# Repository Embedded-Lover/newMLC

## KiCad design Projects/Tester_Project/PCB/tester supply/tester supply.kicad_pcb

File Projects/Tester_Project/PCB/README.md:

# Analog_box_IO_Tester_Hardware

## Getting started

To make it easy for you to get started with GitLab, here's a list of recommended next steps.

Already a pro? Just edit this README.md and make it your own. Want to make it easy? [Use the template at the bottom](#editing-this-readme)!

## Add your files

- [ ] [Create](https://docs.gitlab.com/ee/user/project/repository/web_editor.html#create-a-file) or [upload](https://docs.gitlab.com/ee/user/project/repository/web_editor.html#upload-a-file) files
- [ ] [Add files using the command line](https://docs.gitlab.com/ee/gitlab-basics/add-file.html#add-a-file-using-the-command-line) or push an existing Git repository with the following command:

```
cd existing_repo
git remote add origin https://git.mapnalocomotive.com/ahmadi_y/analog_box_io_tester_hardware.git
git branch -M main
git push -uf origin main
```

## Integrate with your tools

- [ ] [Set up project integrations](https://git.mapnalocomotive.com/ahmadi_y/analog_box_io_tester_hardware/-/settings/integrations)

## Collaborate with your team

- [ ] [Invite team members and collaborators](https://docs.gitlab.com/ee/user/project/members/)
- [ ] [Create a new merge request](https://docs.gitlab.com/ee/user/project/merge_requests/creating_merge_requests.html)
- [ ] [Automatically close issues from merge requests](https://docs.gitlab.com/ee/user/project/issues/managing_issues.html#closing-issues-automatically)
- [ ] [Enable merge request approvals](https://docs.gitlab.com/ee/user/project/merge_requests/approvals/)
- [ ] [Set auto-merge](https://docs.gitlab.com/ee/user/project/merge_requests/merge_when_pipeline_succeeds.html)

## Test and Deploy

Use the built-in continuous integration in GitLab.

- [ ] [Get started with GitLab CI/CD](https://docs.gitlab.com/ee/ci/quick_start/index.html)
- [ ] [Analyze your code for known vulnerabilities with Static Application Security Testing (SAST)](https://docs.gitlab.com/ee/user/application_security/sast/)
- [ ] [Deploy to Kubernetes, Amazon EC2, or Amazon ECS using Auto Deploy](https://docs.gitlab.com/ee/topics/autodevops/requirements.html)
- [ ] [Use pull-based deployments for improved Kubernetes management](https://docs.gitlab.com/ee/user/clusters/agent/)
- [ ] [Set up protected environments](https://docs.gitlab.com/ee/ci/environments/protected_environments.html)

***

# Editing this README

When you're ready to make this README your own, just edit this file and use the handy template below (or feel free to structure it however you want - this is just a starting point!). Thanks to [makeareadme.com](https://www.makeareadme.com/) for this template.

## Suggestions for a good README

Every project is different, so consider which of these sections apply to yours. The sections used in the template are suggestions for most open source projects. Also keep in mind that while a README can be too long and detailed, too long is better than too short. If you think your README is too long, consider utilizing another form of documentation rather than cutting out information.

## Name
Choose a self-explaining name for your project.

## Description
Let people know what your project can do specifically. Provide context and add a link to any reference visitors might be unfamiliar with. A list of Features or a Background subsection can also be added here. If there are alternatives to your project, this is a good place to list differentiating factors.

## Badges
On some READMEs, you may see small images that convey metadata, such as whether or not all the tests are passing for the project. You can use Shields to add some to your README. Many services also have instructions for adding a badge.

## Visuals
Depending on what you are making, it can be a good idea to include screenshots or even a video (you'll frequently see GIFs rather than actual videos). Tools like ttygif can help, but check out Asciinema for a more sophisticated method.

## Installation
Within a particular ecosystem, there may be a common way of installing things, such as using Yarn, NuGet, or Homebrew. However, consider the possibility that whoever is reading your README is a novice and would like more guidance. Listing specific steps helps remove ambiguity and gets people to using your project as quickly as possible. If it only runs in a specific context like a particular programming language version or operating system or has dependencies that have to be installed manually, also add a Requirements subsection.

## Usage
Use examples liberally, and show the expected output if you can. It's helpful to have inline the smallest example of usage that you can demonstrate, while providing links to more sophisticated examples if they are too long to reasonably include in the README.

## Support
Tell people where they can go to for help. It can be any combination of an issue tracker, a chat room, an email address, etc.

## Roadmap
If you have ideas for releases in the future, it is a good idea to list them in the README.

## Contributing
State if you are open to contributions and what your requirements are for accepting them.

For people who want to make changes to your project, it's helpful to have some documentation on how to get started. Perhaps there is a script that they should run or some environment variables that they need to set. Make these steps explicit. These instructions could also be useful to your future self.

You can also document commands to lint the code or run tests. These steps help to ensure high code quality and reduce the likelihood that the changes inadvertently break something. Having instructions for running tests is especially helpful if it requires external setup, such as starting a Selenium server for testing in a browser.

## Authors and acknowledgment
Show your appreciation to those who have contributed to the project.

## License
For open source projects, say how it is licensed.

## Project status
If you have run out of energy or time for your project, put a note at the top of the README saying that development has slowed down or stopped completely. Someone may choose to fork your project or volunteer to step in as a maintainer or owner, allowing your project to keep going. You can also make an explicit request for maintainers.

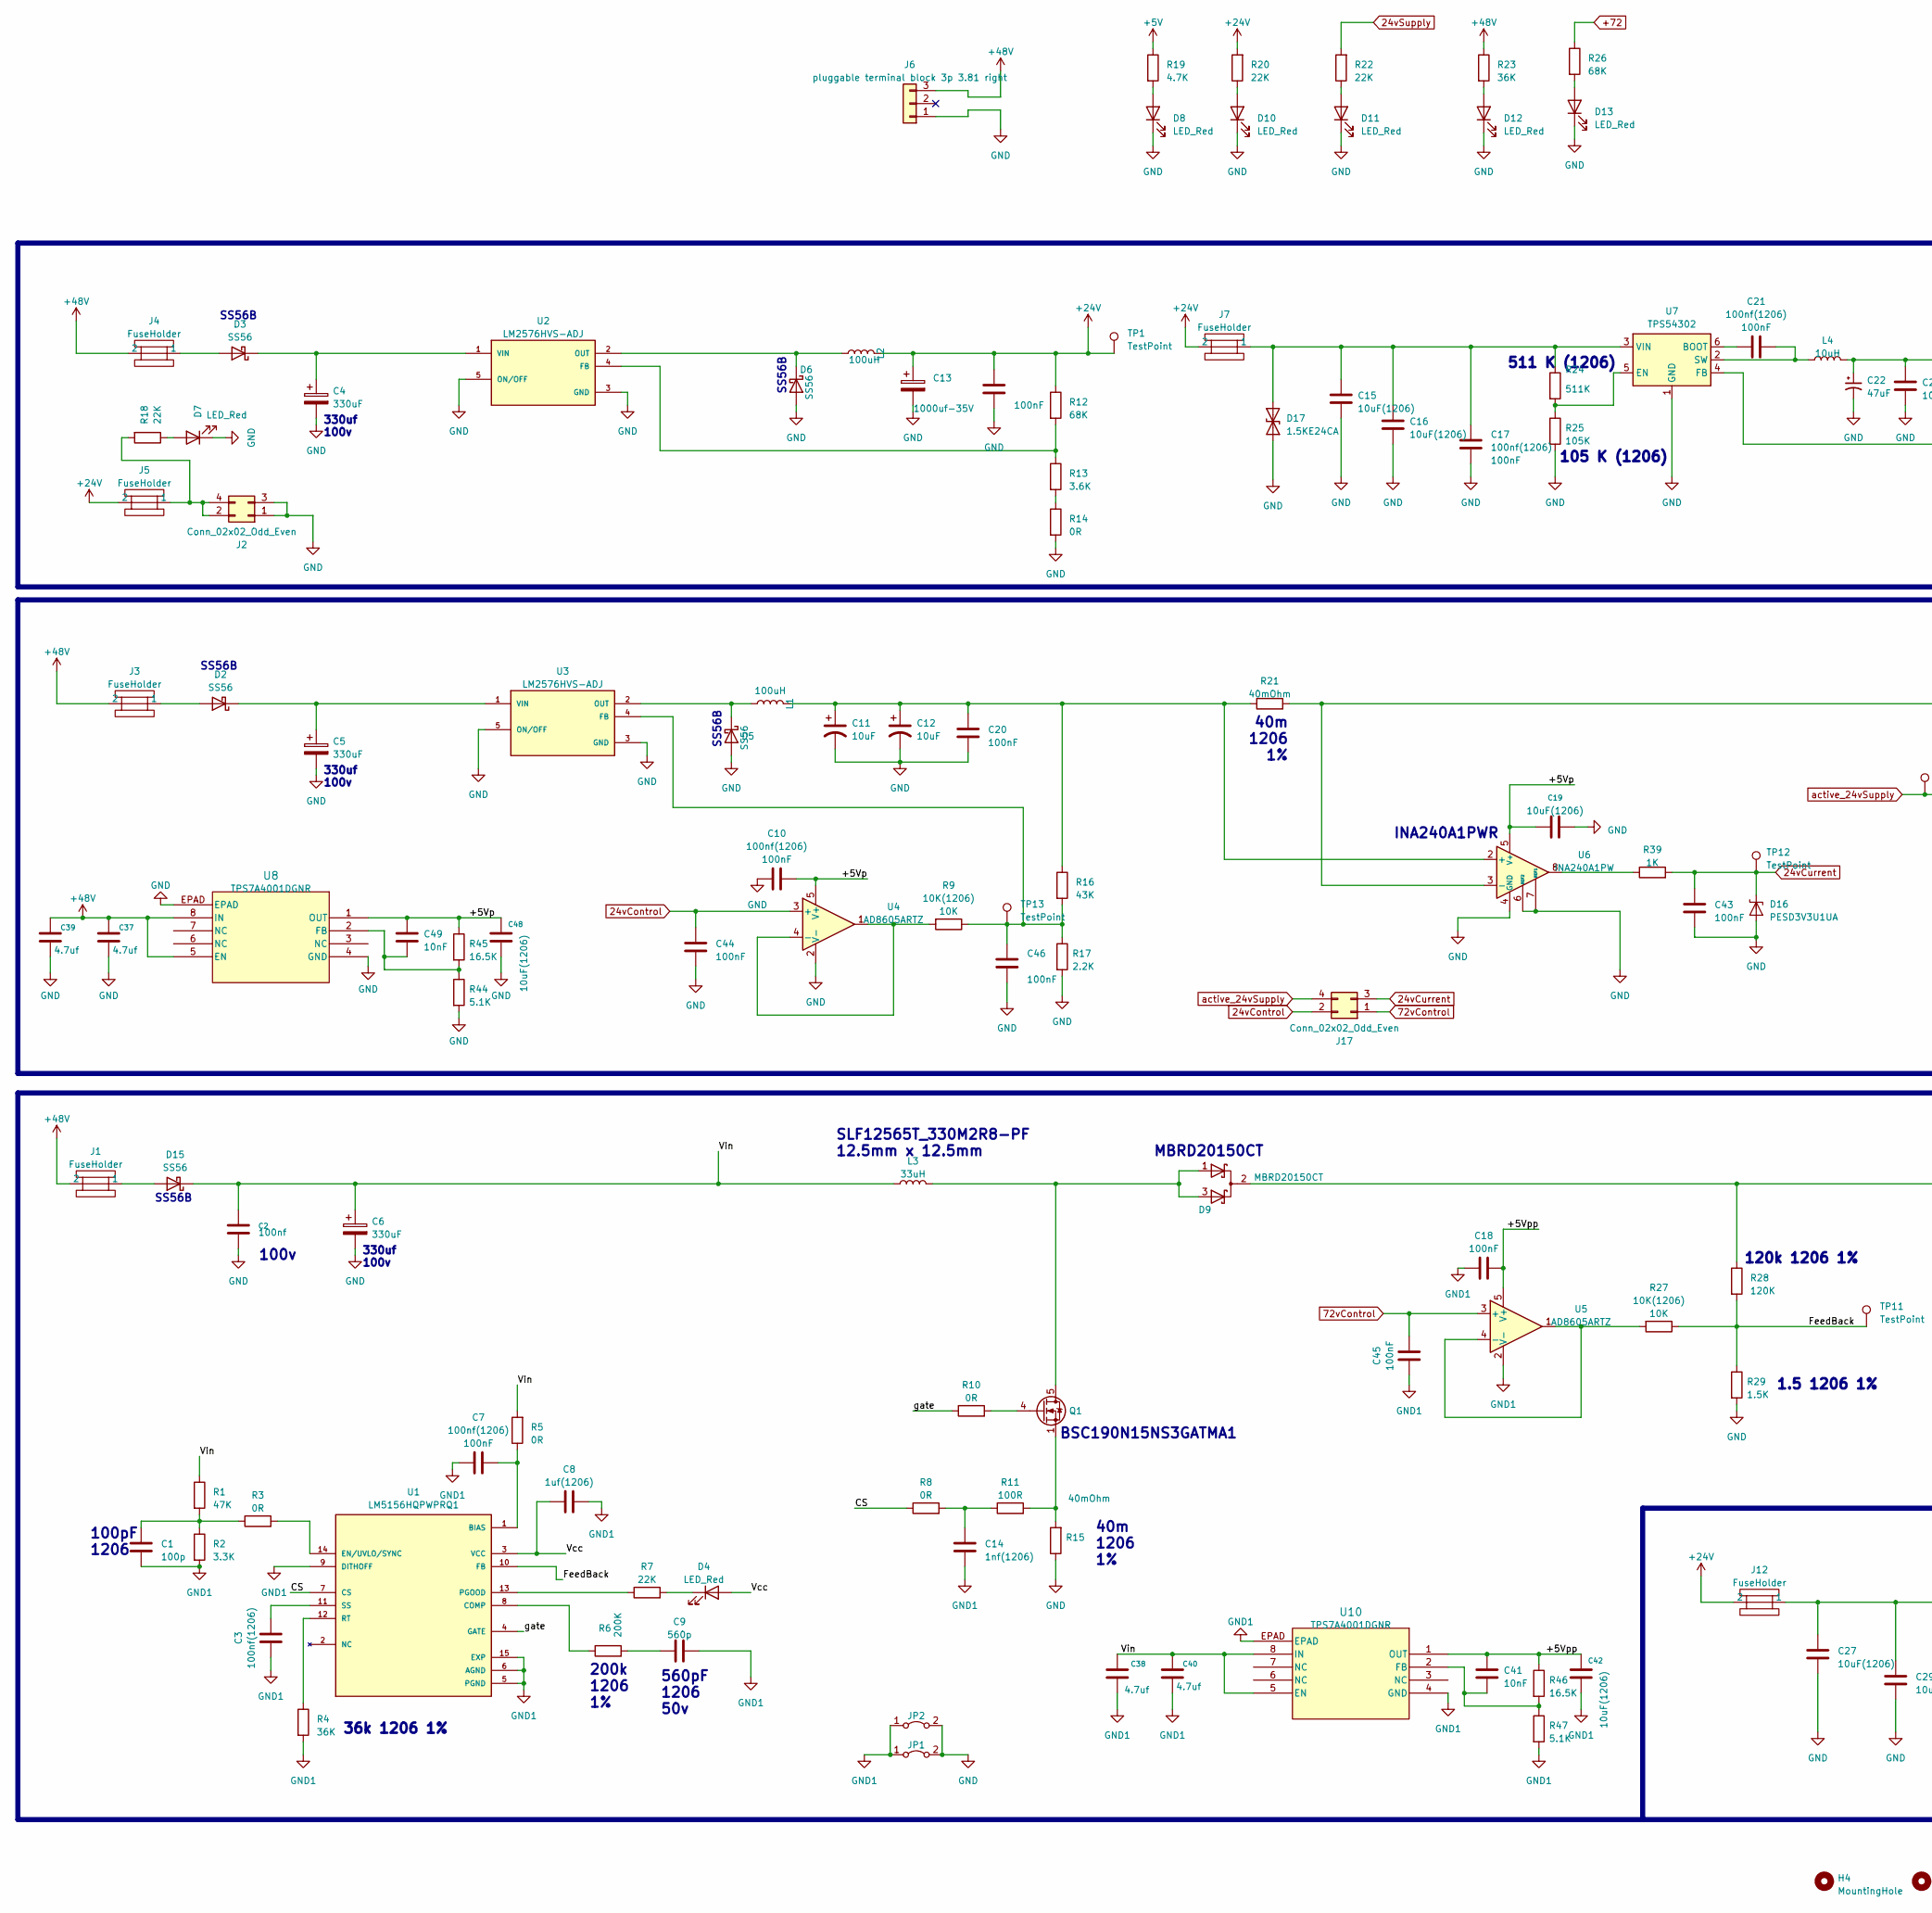
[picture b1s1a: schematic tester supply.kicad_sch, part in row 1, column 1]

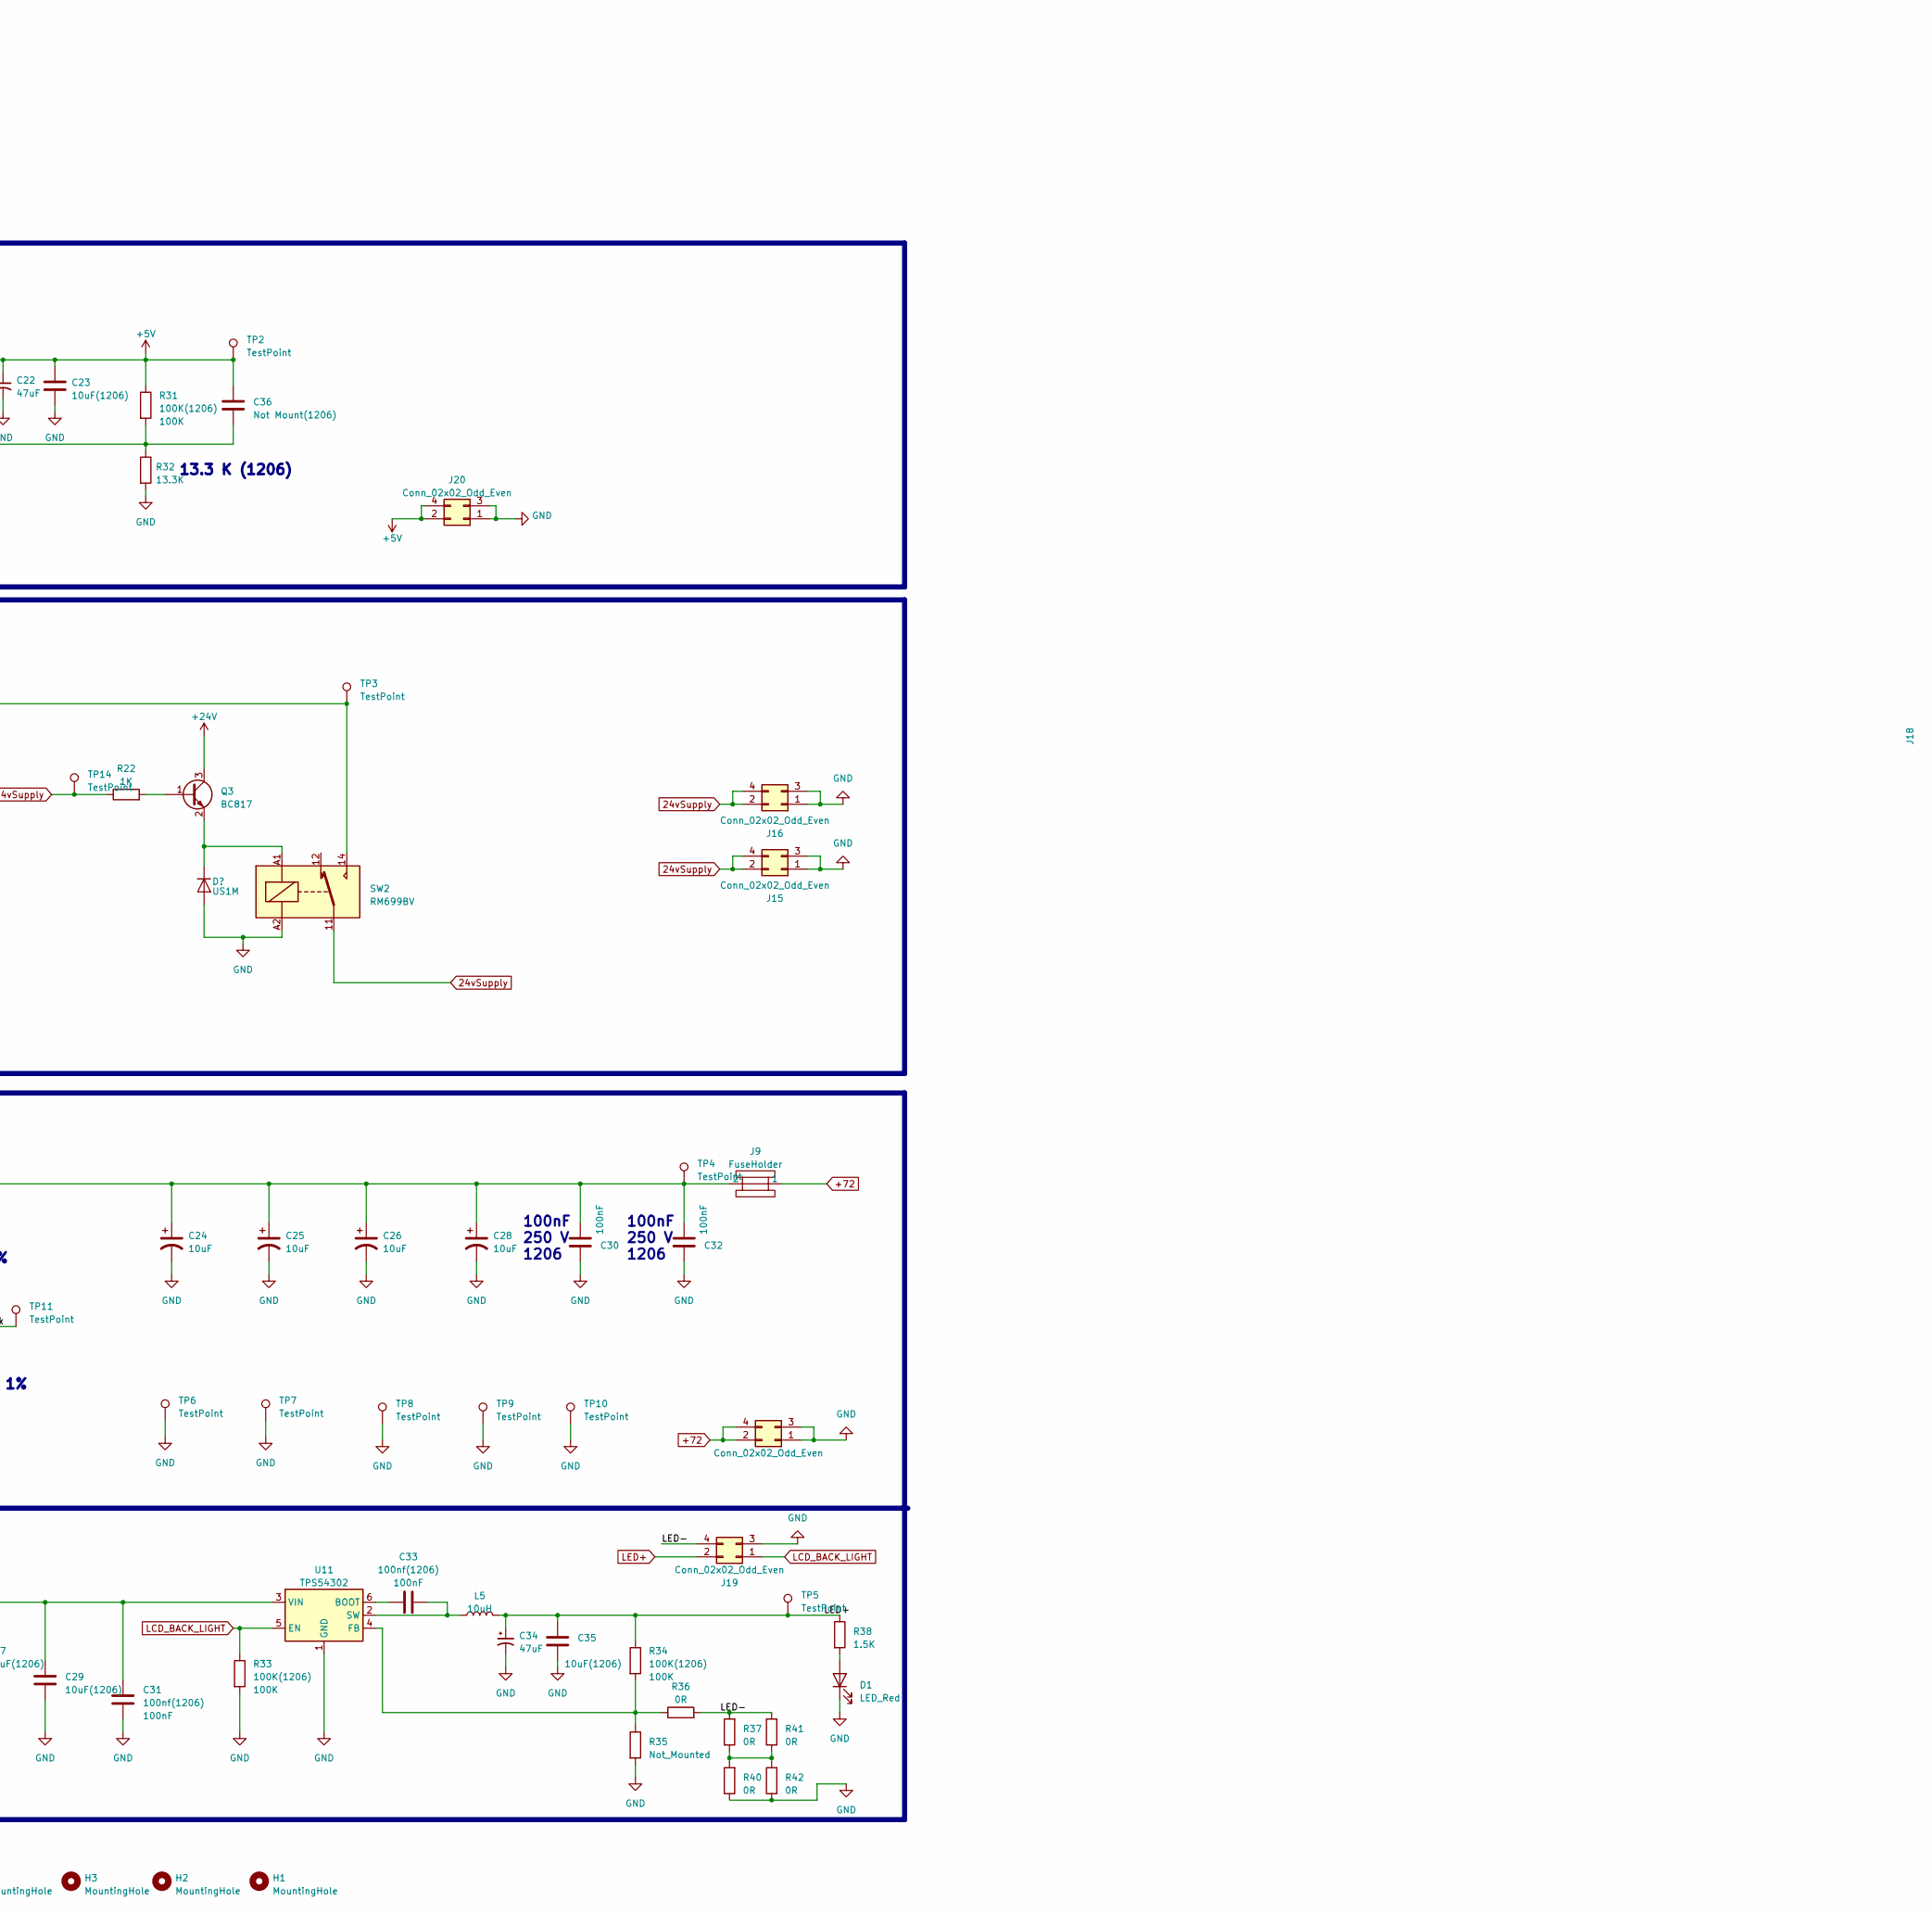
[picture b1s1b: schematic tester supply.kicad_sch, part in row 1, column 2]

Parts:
C1: 100p(1206); C_1206_3216Metric_Pad1.33x1.80mm_HandSolder; MPN C1206C101J5GACAUTO
C2: 100nF(1206)-100V; C_1206_3216Metric_Pad1.33x1.80mm_HandSolder; MPN CGA5L1C0G2A104J160AC
C3, C7, C10, C17, C18, C20, C21, C31, C33, C43, C44, C45, C46, C47: 100nf(1206); C_1206_3216Metric_Pad1.33x1.80mm_HandSolder; MPN CGA5L2X7R2A104K160AE
C4, C5, C6: 330uf-100V; CP_Radial_D16.0mm_P7.50mm; MPN UPW2A331MHD
C8: 1uf(1206); C_1206_3216Metric_Pad1.33x1.80mm_HandSolder; MPN CGA5L3X7R1H105K160AE
C9: 560p(1206); C_1206_3216Metric_Pad1.33x1.80mm_HandSolder; MPN C1206C561F5GACTU
C11, C12: 10uf-50V-solid; CP_Radial_D4.0mm_P2.00mm; MPN A759BQ106M1HAAE090
C13: 1000uf-35V; CP_Radial_D13.0mm_P5.00mm
C14: 1nf(1206); C_1206_3216Metric_Pad1.33x1.80mm_HandSolder; MPN CGA5H4X7R2J102K115AE
C15, C16, C19, C23, C27, C29, C35, C42, C48: 10uF(1206); C_1206_3216Metric_Pad1.33x1.80mm_HandSolder; MPN CGA5L1X7R1H106K160AE
C22, C34: 47uf-35v-solid; CP_Radial_D8.0mm_P3.80mm; MPN RNU1V470MCN1
C24, C25, C26, C28: 10uf-160V; CP_Radial_D10.0mm_P5.00mm; MPN ECA-2CHG100B
C30, C32: 100nf(1206)-250V; C_1206_3216Metric_Pad1.33x1.80mm_HandSolder; MPN C1206C104KARECAUTO
C36: Not Mount(1206); C_1206_3216Metric_Pad1.33x1.80mm_HandSolder
C37, C38, C39, C40: 4.7uF(0805) -100V; C_0805_2012Metric_Pad1.18x1.45mm_HandSolder; MPN C2012X5R2A475K125AC
C41, C49: 10nf(1206); C_1206_3216Metric_Pad1.33x1.80mm_HandSolder; MPN CGA5H4X7R2J103K115AE
D1, D4, D7, D8, D10, D11, D12, D13: LED_RED(1206); LED_1206_3216Metric_Castellated; MPN 150120SS75000
D2, D3, D5, D6, D15: SS56-smc; D_SMC; MPN SS56ALH
D9: MBRD20150CT; TO-252-2; MPN MBRD20150CT
D16: PESD3V3U1UA,115; D_SOD-323_HandSoldering; MPN PESD3V3U1UA,115
D17: 1.5KE24CA; D_DO-201AE_P15.24mm_Horizontal; MPN 1.5KE24CA
D21: US1M; D_SMA; MPN US1MHE3_A/H
H1, H2, H3, H4: MountingHole; MountingHole_4.3mm_M4_Pad_Via
J1, J3, J4, J5, J7, J9, J12: Fuse1808Holder; fuse.holder.1808-1; MPN 01550900M
J2, J15, J16, J17, J18, J19, J20: Conn_02x02_Odd_Even; 4p header reverse
J6: pluggable terminal block 3p 3.81 right; PhoenixContact_MC_1,5_3-G-3.81_1x03_P3.81mm_Horizontal; MPN WJ15EDGRC-3.81-3P
JP1, JP2: Jumper_2_Bridged; SolderJumper-2_P1.3mm_Bridged_RoundedPad1.0x1.5mm
L1, L2: SLF12565T-101M1R6-PF; L_12x12mm_H8mm; MPN SLF12565T-101M1R6-PF
L3: 330uh-smd-12.5mm; L_TaiTech_TMPC1265_13.5x12.5mm; MPN SRR1260A-330M
L4, L5: 10uh-smd-12*12; L_12x12mm_; MPN SLF12565T-100M1R6-PF
Q1: BSC196N10NSG; TDSON-8-1; MPN BSC190N15NS3GATMA1
Q3: BC817-smd; SOT-23W_Handsoldering; MPN BC817K-25R
R1: 47K(1206); R_1206_3216Metric_Pad1.30x1.75mm_HandSolder; MPN RN73R2BTTD4702F25
R2: 3.3k(1206); R_1206_3216Metric_Pad1.30x1.75mm_HandSolder; MPN RN73R2BTTD3301F25
R3, R5, R8, R10, R14, R36, R37, R40, R41, R42: 0R(1206); R_1206_3216Metric_Pad1.30x1.75mm_HandSolder; MPN CRCW12060000Z0EB
R4, R23: 36k(1206); R_1206_3216Metric_Pad1.30x1.75mm_HandSolder; MPN RN73R2BTTD3602F25
R6: 200k(1206); R_1206_3216Metric_Pad1.30x1.75mm_HandSolder; MPN RN73H2BTTD2003F
R7, R18, R20: 22K(1206); R_1206_3216Metric_Pad1.30x1.75mm_HandSolder; MPN RN73R2BTTD2202F25
R9, R27: 10K(1206); R_1206_3216Metric_Pad1.30x1.75mm_HandSolder; MPN RN73R2BTTD1002F25
R11: 100R(1206); R_1206_3216Metric_Pad1.42x1.75mm_HandSolder; MPN RN73R2BTTD100RF25
R12, R26: 68K(1206); R_1206_3216Metric_Pad1.30x1.75mm_HandSolder; MPN RN73R2BTTD6802F25
R13: 3.6K(1206); R_1206_3216Metric_Pad1.30x1.75mm_HandSolder; MPN RN73R2BTTD3601F25
R15, R21: 40mOhm(1206); R_1206_3216Metric_Pad1.30x1.75mm_HandSolder; MPN RLS12FTCR040
R16: 43K(1206); R_1206_3216Metric_Pad1.30x1.75mm_HandSolder; MPN RK73G2BRTTD4302F
R17: 2.2K(1206); R_1206_3216Metric_Pad1.30x1.75mm_HandSolder; MPN RN73R2BTTD2201F25
R19: 4.7K(1206); R_1206_3216Metric_Pad1.30x1.75mm_HandSolder; MPN RN73R2BTTD4701F25
R22, R39: 1k(1206); R_1206_3216Metric_Pad1.30x1.75mm_HandSolder; MPN RN73R2BTTD1001F25
R24: 511K(1206); R_1206_3216Metric_Pad1.30x1.75mm_HandSolder; MPN RK73H2ATTD5113F
R25: 105K(1206); R_1206_3216Metric_Pad1.30x1.75mm_HandSolder; MPN RK73H2ARTTD1053F
R28: 120k(1206); R_1206_3216Metric_Pad1.30x1.75mm_HandSolder; MPN RK73H2BTTD1203F
R29, R38: 1.5K(1206); R_1206_3216Metric_Pad1.30x1.75mm_HandSolder; MPN RN73R2BTTD1501F25
R31, R33, R34: 100K(1206); R_1206_3216Metric_Pad1.30x1.75mm_HandSolder; MPN RN73R2BTTD1003F25
R32: 13.3K(1206); R_1206_3216Metric_Pad1.30x1.75mm_HandSolder; MPN RK73H2ARTTD1332F
R35: Not_Mounted(0805); R_0805_2012Metric_Pad1.20x1.40mm_HandSolder
R44, R47: 5.1k(0805); R_0805_2012Metric_Pad1.20x1.40mm_HandSolder; MPN RN73R2ATTD5101F25
R45, R46: 16.5K(0805); R_0805_2012Metric_Pad1.20x1.40mm_HandSolder; MPN RC0805FR-0716K5L
SW2: RM699BV-3011-85-1024; RM699BV
TP1, TP2, TP3, TP4, TP5, TP6, TP7, TP8, TP9, TP10: TestPoint; TestPoint_Loop_D2.50mm_Drill1.0mm
TP11, TP12, TP13, TP14: TestPoint; TestPoint_Keystone_5000-5004_Miniature
U1: LM5156HQPWPRQ1; IC_LM5156HPWPR; MPN LM5156HQPWPRQ1
U2, U3: LM2576HVS-ADJ; TO-263-5_TabPin3; MPN LM2576HVS-ADJ/NOPB
U4, U5: AD8605ARTZ; TSOT-23-5
U6: INA240A1PW; TSSOP-8_4.4x3mm_P0.65mm; MPN INA240A1PWR
U7, U11: TPS54302DDCR; SOT-23-6_Handsoldering; MPN TPS54302DDCR
U8, U10: TPS7A4001DGNR; MSOP-8-1EP_3x3mm_P0.65mm_EP1.73x1.85mm_ThermalVias; MPN TPS7A4001DGNR

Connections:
24vControl: C44.1, J17.2, U4.3 (+)
24vCurrent: C43.1, D16.1 (A1), J17.3, R39.2, TP12.1
72vControl: C45.2, J17.1, U5.3 (+)
+5V: C22.1, C23.1, C36.1, J20.2, J20.4, L4.2, R19.1, R31.1, TP2.1
+24V: C13.1, C47.1, J5.2, J7.2, J12.2, L2.2, R12.1, R20.2, TP1.1; also elsewhere on the board
+48V: C37.1, C39.1, J1.2, J3.2, J4.2, J6.3, R23.1, U8.5 (EN), U8.8 (IN)
+72: J9.1, J18.2, J18.4, R26.1
/+5Vp: C10.2, C19.1, C48.1, C49.1, R45.1, U4.5 (V+), U6.5 (V+), U8.1 (OUT)
/+5Vpp: C18.2, C41.1, C42.1, R46.1, U5.5 (V+), U10.1 (OUT)
/CS: R8.1, U1.7 (CS)
/FeedBack: R27.1, R28.2, R29.1, TP11.1, U1.10 (FB)
/LED-: J19.4, R36.2, R37.2, R41.2
/Vcc: C8.1, D4.2 (A), U1.3 (VCC)
/Vin: C2.1, C6.1, C38.1, C40.1, D15.1 (K), L3.1, R1.1, R5.2, U10.5 (EN), U10.8 (IN)
/gate: R10.1, U1.4 (GATE)
GND: C2.2, C4.2, C5.2, C6.2, C10.1, C11.2, C12.2, C13.2, C15.2, C16.2, C17.2, C19.2, C20.2, C22.2, C23.2, C24.2, C25.2, C26.2, C27.2, C28.2, C29.2, C30.2, C31.2, C32.2, C34.2, C35.2, C37.2, C39.2, C43.2, C44.2, C46.1, C47.2, C48.2, D1.1 (K), D5.2 (A), D6.2 (A), D7.1 (K), D8.1 (K), D10.1 (K), D11.1 (K), D12.1 (K), D13.1 (K), D16.2 (A2), D17.1 (A1), J2.1, J2.3, J6.1, J15.1, J15.3, J16.1, J16.3, J18.1, J18.3, J19.3, J20.1, J20.3, JP1.2 (B), JP2.2 (B), R14.2, R15.1, R17.2, R25.2, R29.2, R32.2, R33.2, R35.2, R40.1, R42.1, R44.2, TP6.1, TP7.1, TP8.1, TP9.1, TP10.1, U2.3 (GND), U2.5 (ON/OFF), U3.3 (GND), U3.5 (ON/OFF), U4.2 (V-), U6.1 (GND), U6.4 (GND), U6.6 (REF2), U6.7 (REF1), U7.1 (GND), U8.4 (GND), U8.EPAD, U11.1 (GND); also elsewhere on the board
GND1: C1.2, C3.1, C7.1, C8.2, C9.2, C14.2, C18.1, C38.2, C40.2, C42.2, C45.1, JP1.1 (A), JP2.1 (A), R2.2, R4.2, R47.2, U1.5 (PGND), U1.6 (AGND), U1.9 (DITHOFF), U1.15 (EXP), U5.2 (V-), U10.4 (GND), U10.EPAD
LCD_BACK_LIGHT: J19.1, R33.1, U11.5 (EN)
LED+: C34.1, C35.1, J19.2, L5.2, R34.1, R38.1, TP5.1
unnamed: C1.1, R1.2, R2.1, R3.1
unnamed: C9.1, R6.2
unnamed: C14.1, R8.2, R11.1
unnamed: D1.2 (A), R38.2
unnamed: D2.2 (A), J3.1
unnamed: C5.1, D2.1 (K), U3.1 (VIN)
unnamed: D3.2 (A), J4.1
unnamed: C4.1, D3.1 (K), U2.1 (VIN)
unnamed: D4.1 (K), R7.2
unnamed: D5.1 (K), L1.1, U3.2 (OUT)
unnamed: D6.1 (K), L2.1, U2.2 (OUT)
unnamed: D7.2 (A), R18.1
unnamed: D8.2 (A), R19.2
unnamed: C24.1, C25.1, C26.1, C28.1, C30.1, C32.1, D9.2 (A), J9.2, R28.1, TP4.1
unnamed: D10.2 (A), R20.1
unnamed: D12.2 (A), R23.2
unnamed: D13.2 (A), R26.2
unnamed: D15.2 (A), J1.1
unnamed: C15.1, C16.1, C17.1, D17.2 (A2), J7.1, R24.1, U7.3 (VIN)
unnamed: J2.2, J2.4, J5.1, R18.2
unnamed: D9.1 (K), D9.3 (K), L3.2, Q1.5 (D)
unnamed: Q1.4 (G), R10.2
unnamed: Q1.1 (S), Q1.2 (S), Q1.3 (S), R11.2, R15.2
unnamed: R13.2, R14.1
unnamed: R37.1, R40.2, R41.1, R42.2
unnamed: R39.1, U6.8
unnamed: C7.2, R5.1, U1.1 (BIAS)
unnamed: R6.1, U1.8 (COMP)
unnamed: R3.2, U1.14 (EN/UVLO/SYNC)
unnamed: R7.1, U1.13 (PGOOD)
unnamed: R4.1, U1.12 (RT)
unnamed: C3.2, U1.11 (SS)
unnamed: R12.2, R13.1, U2.4 (FB)
unnamed: C46.2, R9.1, R16.2, R17.1, TP13.1, U3.4 (FB)
unnamed: R9.2, U4.1, U4.4 (-)
unnamed: R27.2, U5.1, U5.4 (-)
unnamed: C11.1, C12.1, C20.1, L1.2, R16.1, R21.1, U6.2 (+)
unnamed 57: R21.2, TP3.1, U6.3 (-); also elsewhere on the board
unnamed: C21.1, U7.6 (BOOT)
unnamed: R24.2, R25.1, U7.5 (EN)
unnamed: C36.2, R31.2, R32.1, U7.4 (FB)
unnamed: C21.2, L4.1, U7.2 (SW)
unnamed: C49.2, R44.1, R45.2, U8.2 (FB)
unnamed: C41.2, R46.2, R47.1, U10.2 (FB)
unnamed: C33.1, U11.6 (BOOT)
unnamed: R34.2, R35.1, R36.1, U11.4 (FB)
unnamed: C33.2, L5.1, U11.2 (SW)
unnamed: C27.1, C29.1, C31.1, J12.1, U11.3 (VIN)

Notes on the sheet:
330uf 100v
100pF 1206
SS56B
BSC190N15NS3GATMA1
120k 1206 1%
200k 1206 1%
105 K (1206)
100v
MBRD20150CT
36k 1206 1%
511 K (1206)
100nF 250 V 1206
13.3 K (1206)
40m 1206 1%
SLF12565T_330M2R8-PF 12.5mm x 12.5mm
1.5 1206 1%
INA240A1PWR
560pF 1206 50v

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
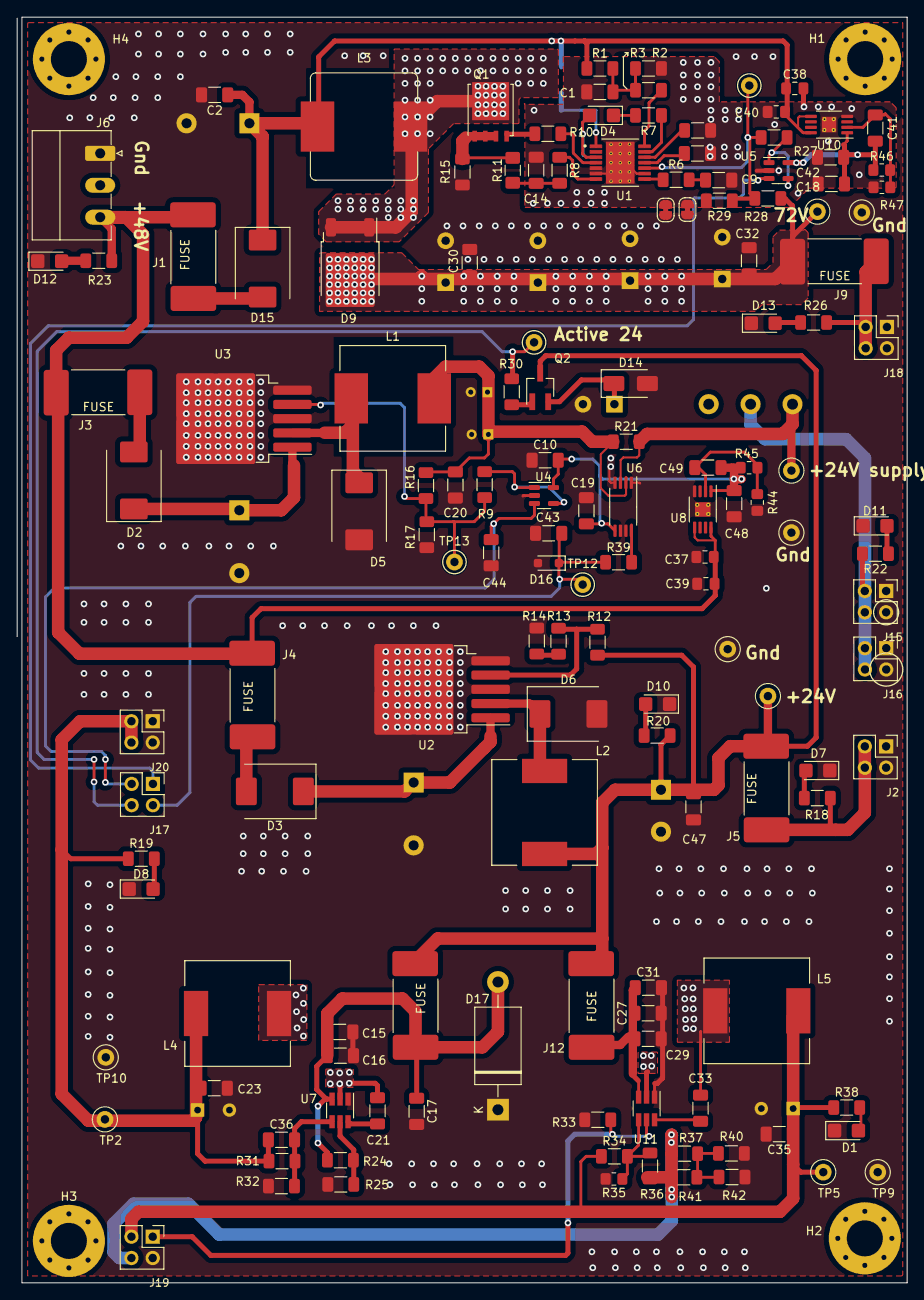
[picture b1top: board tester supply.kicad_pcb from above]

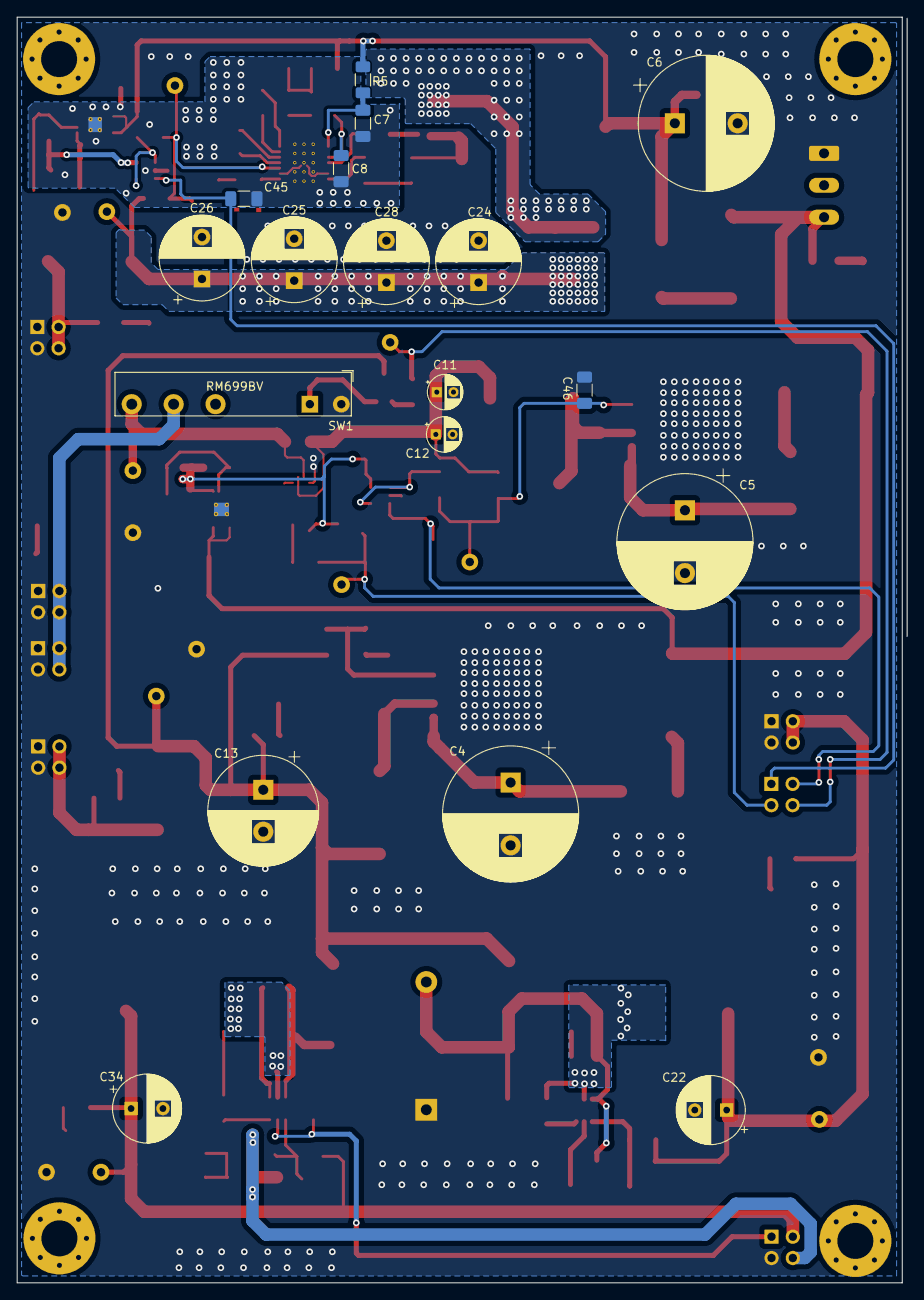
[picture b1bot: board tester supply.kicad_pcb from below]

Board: 2 copper layers, 106.2 x 151.0 mm, 165 parts (18 on the bottom side), 72 nets.

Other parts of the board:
D14: US1M; D_SMA
Q2: BC817-smd; SOT-23W_Handsoldering
R30: 1k(1206); R_1206_3216Metric_Pad1.30x1.75mm_HandSolder
SW1: RM699BV-3011-85-1024; RM699BV

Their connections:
+24V: Q2.3 (C); also elsewhere on the board
GND: D14.2 (A), SW1.A2; also elsewhere on the board
unnamed: D14.1 (K), Q2.2 (E), SW1.A1
unnamed 57: SW1.14; also elsewhere on the board

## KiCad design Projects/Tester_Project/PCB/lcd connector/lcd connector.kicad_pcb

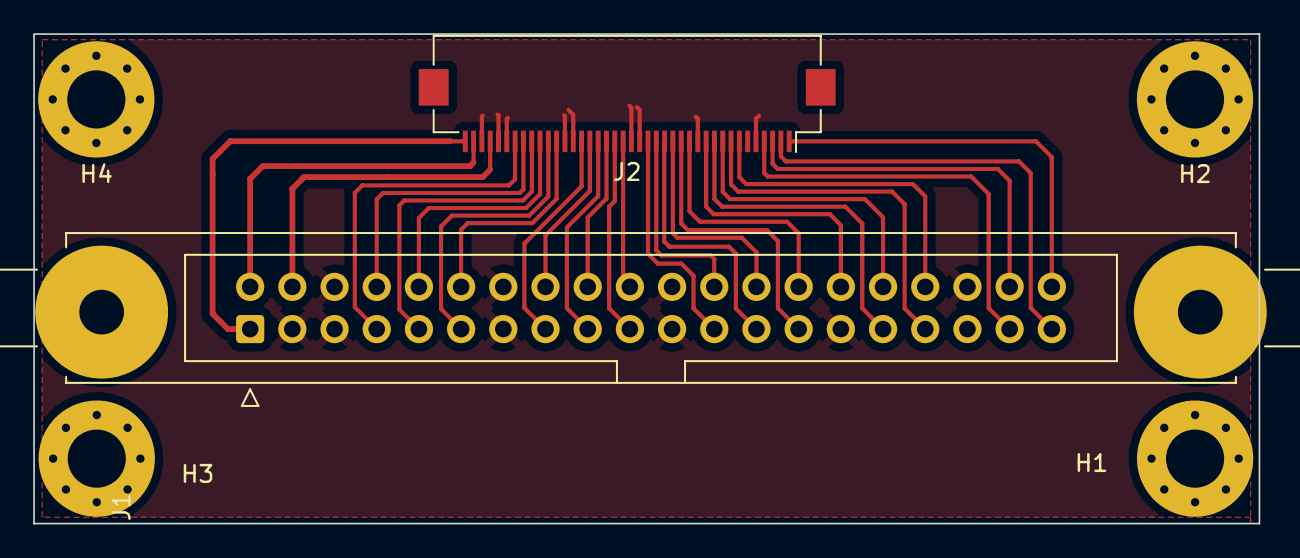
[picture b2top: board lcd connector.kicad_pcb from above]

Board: 2 copper layers, 73.8 x 29.5 mm, 6 parts (0 on the bottom side), 31 nets.

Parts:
H1, H2, H3, H4: MountingHole; MountingHole_3.5mm_Pad_Via
J1: PHL-2*20-STRAIGHT-2.54mm; PHL_2x20_Vertical
J2: Conn_01x40_Socket; FPC-40way_P0.50mm_Horizontal

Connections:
+3.3V: J1.4, J2.4
/LED-: J1.1, J2.1
/Touch_X+: J1.37, J2.37
/Touch_X-: J1.39, J2.39
/Touch_Y+: J1.40, J2.40
/Touch_Y-: J1.38, J2.38
GND: J1.3, J1.5, J1.6, J1.13, J1.14, J1.21, J1.22, J1.29, J1.36, J2.3, J2.5, J2.6, J2.13, J2.14, J2.21, J2.22, J2.29, J2.36
LCD_B2: J1.23, J2.23
LCD_B4: J1.25, J2.25
LCD_B5: J1.26, J2.26
LCD_B6: J1.27, J2.27
LCD_B7: J1.28, J2.28
LCD_BACK_LIGHT: J1.31, J2.31
LCD_CLK: J1.30, J2.30
LCD_DE: J1.34, J2.34
LCD_G2: J1.15, J2.15
LCD_G3: J1.16, J2.16
LCD_G4: J1.17, J2.17
LCD_G5: J1.18, J2.18
LCD_G6: J1.19, J2.19
LCD_G7: J1.20, J2.20
LCD_HS: J1.32, J2.32
LCD_R2: J1.7, J2.7
LCD_R3: J1.8, J2.8
LCD_R4: J1.9, J2.9
LCD_R5: J1.10, J2.10
LCD_R6: J1.11, J2.11
LCD_R7: J1.12, J2.12
LCD_VS: J1.33, J2.33
LDC_B3: J1.24, J2.24
LED+: J1.2, J2.2
